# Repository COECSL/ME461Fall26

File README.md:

# ME461Fall26
Lab and HW assignment repository for ME461 Fall 2026

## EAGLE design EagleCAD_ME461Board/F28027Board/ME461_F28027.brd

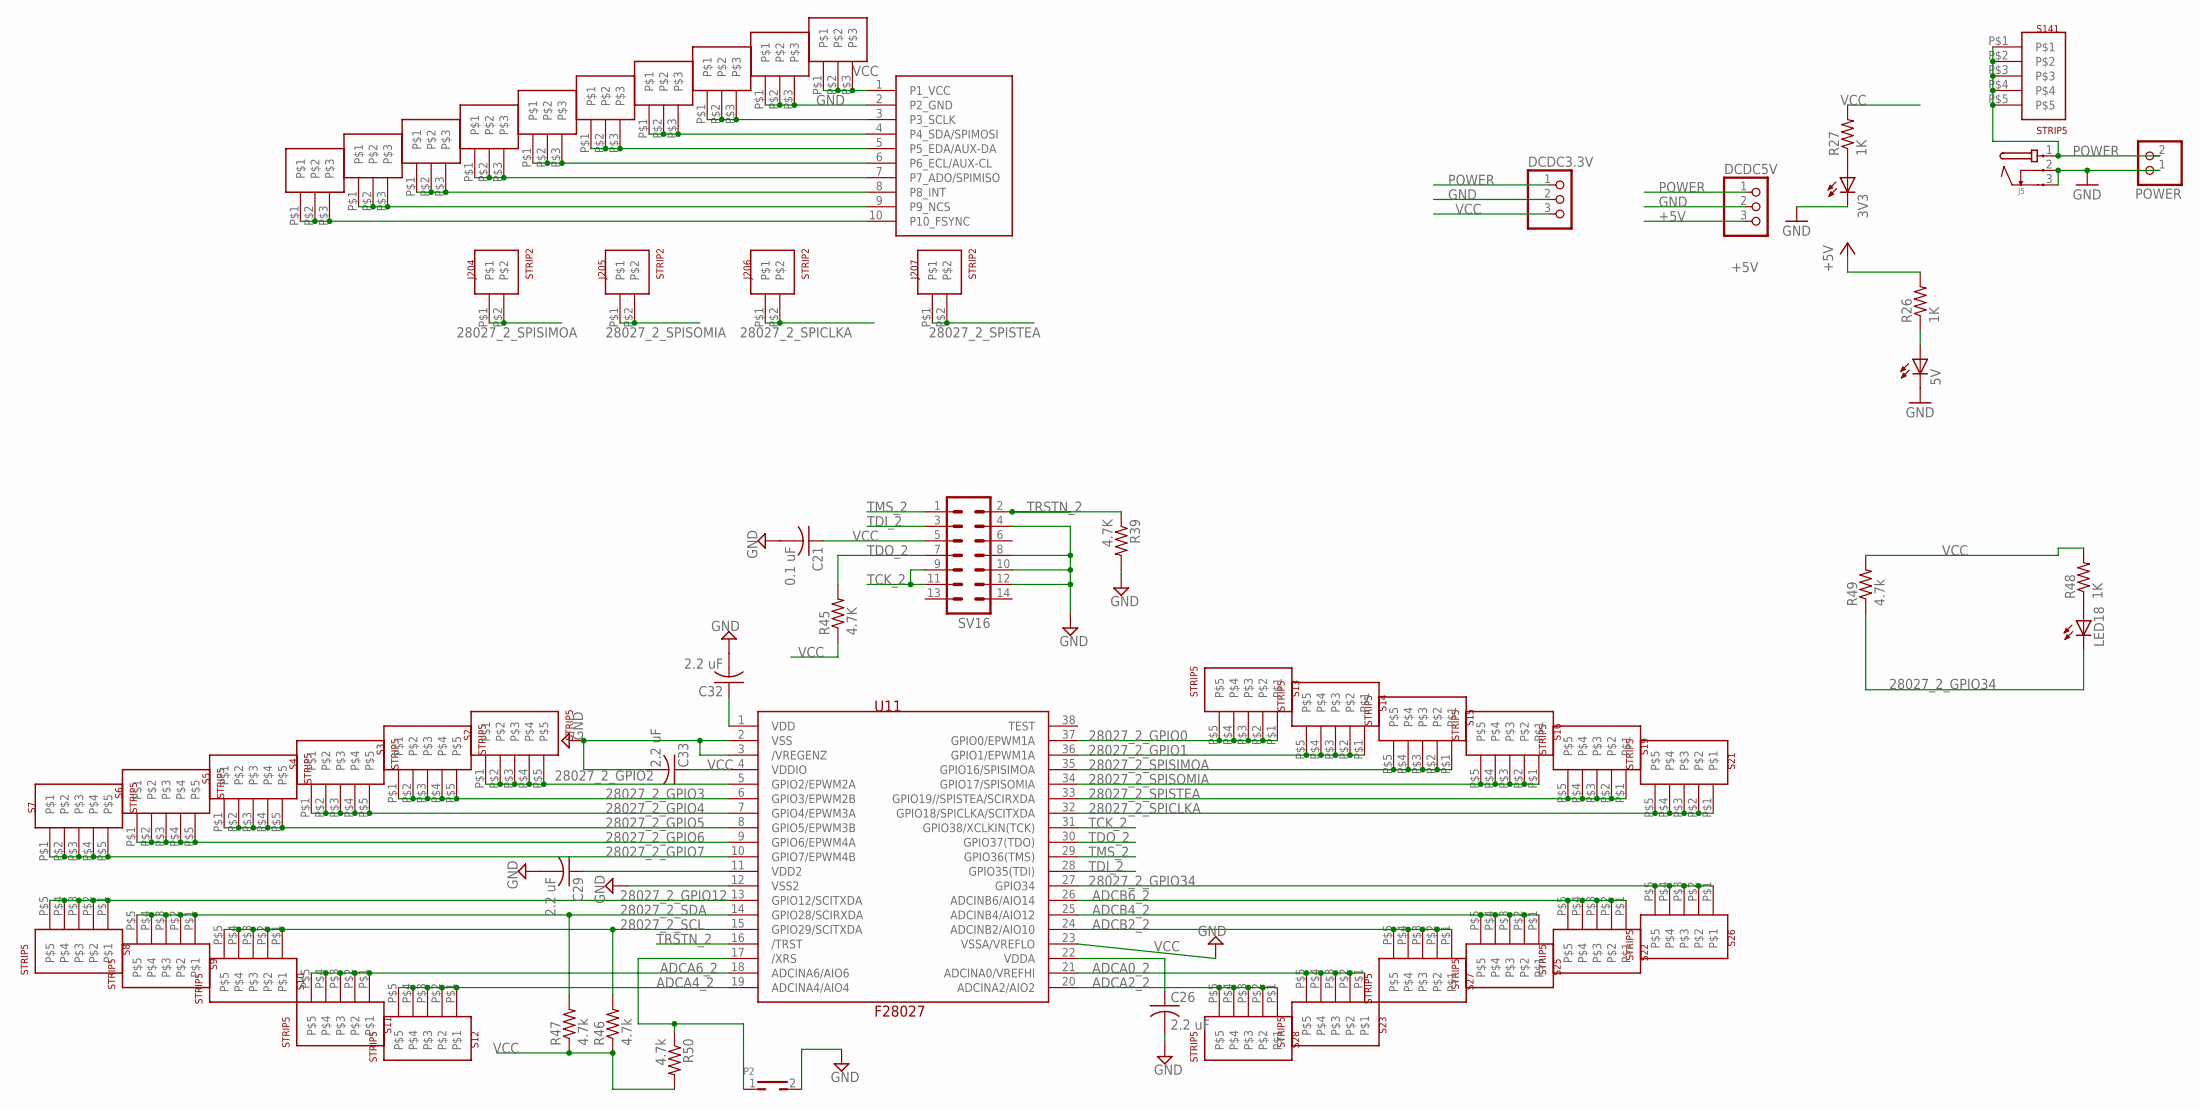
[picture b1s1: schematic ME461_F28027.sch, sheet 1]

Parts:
3V3, 5V: LEDCHIPLED_1206; CHIPLED_1206
C21: 0.1 uF; C1206
C26, C29, C32, C33: 2.2 uF; C1206
DCDC3.3V, DCDC5V: PINHD-1X3; 1X03
J5: JACK-PMS
J123, J124, J125, J126, J127, J128, J129, J130, J131, J132: STRIP3
J204, J205, J206, J207: STRIP2
LED18: LEDCHIPLED_1206; CHIPLED_1206
P2: TH_PUSHBOTTON; TH_PUSHBUTTON
POWER: PINHD-1X2; 1X02
R26, R27, R48: 1K; M1206
R39, R45: 4.7K; M1206
R46, R47, R49, R50: 4.7k; M1206
S2, S3, S4, S5, S6, S7, S8, S9, S10, S11, S12, S13, S14, S15, S16, S19, S21, S22, S23, S25, S26, S27, S28, S141: STRIP5
SV16: MA07-2
U11: F28027; DA38
U$1: MPU-9250-BB

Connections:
28027_2_GPIO0: S13.P$1, S13.P$2, S13.P$3, S13.P$4, S13.P$5, U11.37 (GPIO0/EPWM1A); also elsewhere on the board
28027_2_GPIO1: S14.P$1, S14.P$2, S14.P$3, S14.P$4, S14.P$5, U11.36 (GPIO1/EPWM1A); also elsewhere on the board
28027_2_GPIO2: S2.P$1, S2.P$2, S2.P$3, S2.P$4, S2.P$5, U11.5 (GPIO2/EPWM2A); also elsewhere on the board
28027_2_GPIO3: S3.P$1, S3.P$2, S3.P$3, S3.P$4, S3.P$5, U11.6 (GPIO3/EPWM2B); also elsewhere on the board
28027_2_GPIO4: S4.P$1, S4.P$2, S4.P$3, S4.P$4, S4.P$5, U11.7 (GPIO4/EPWM3A); also elsewhere on the board
28027_2_GPIO5: S5.P$1, S5.P$2, S5.P$3, S5.P$4, S5.P$5, U11.8 (GPIO5/EPWM3B); also elsewhere on the board
28027_2_GPIO6: S6.P$1, S6.P$2, S6.P$3, S6.P$4, S6.P$5, U11.9 (GPIO6/EPWM4A); also elsewhere on the board
28027_2_GPIO7: S7.P$1, S7.P$2, S7.P$3, S7.P$4, S7.P$5, U11.10 (GPIO7/EPWM4B); also elsewhere on the board
28027_2_GPIO12: S8.P$1, S8.P$2, S8.P$3, S8.P$4, S8.P$5, U11.13 (GPIO12/SCITXDA); also elsewhere on the board
28027_2_GPIO34: LED18.C, R49.1, S26.P$1, S26.P$2, S26.P$3, S26.P$4, S26.P$5, U11.27 (GPIO34); also elsewhere on the board
28027_2_SCL: R46.2, S10.P$1, S10.P$2, S10.P$3, S10.P$4, S10.P$5, U11.15 (GPIO29/SCITXDA); also elsewhere on the board
28027_2_SDA: R47.2, S9.P$1, S9.P$2, S9.P$3, S9.P$4, S9.P$5, U11.14 (GPIO28/SCIRXDA); also elsewhere on the board
28027_2_SPICLKA: J206.P$1, J206.P$2, S21.P$1, S21.P$2, S21.P$3, S21.P$4, S21.P$5, U11.32 (GPIO18/SPICLKA/SCITXDA); also elsewhere on the board
28027_2_SPISIMOA: J204.P$1, J204.P$2, S15.P$1, S15.P$2, S15.P$3, S15.P$4, S15.P$5, U11.35 (GPIO16/SPISIMOA); also elsewhere on the board
28027_2_SPISOMIA: J205.P$1, J205.P$2, S16.P$1, S16.P$2, S16.P$3, S16.P$4, S16.P$5, U11.34 (GPIO17/SPISOMIA); also elsewhere on the board
28027_2_SPISTEA: J207.P$1, J207.P$2, S19.P$1, S19.P$2, S19.P$3, S19.P$4, S19.P$5, U11.33 (GPIO19//SPISTEA/SCIRXDA)
+5V: DCDC5V.3, R26.2; also elsewhere on the board
ADCA0_2: S23.P$1, S23.P$2, S23.P$3, S23.P$4, S23.P$5, U11.21 (ADCINA0/VREFHI); also elsewhere on the board
ADCA2_2: S28.P$1, S28.P$2, S28.P$3, S28.P$4, S28.P$5, U11.20 (ADCINA2/AIO2); also elsewhere on the board
ADCA4_2: S12.P$1, S12.P$2, S12.P$3, S12.P$4, S12.P$5, U11.19 (ADCINA4/AIO4); also elsewhere on the board
ADCA6_2: S11.P$1, S11.P$2, S11.P$3, S11.P$4, S11.P$5, U11.18 (ADCINA6/AIO6); also elsewhere on the board
ADCB2_2: S27.P$1, S27.P$2, S27.P$3, S27.P$4, S27.P$5, U11.24 (ADCINB2/AIO10); also elsewhere on the board
ADCB4_2: S25.P$1, S25.P$2, S25.P$3, S25.P$4, S25.P$5, U11.25 (ADCINB4/AIO12); also elsewhere on the board
ADCB6_2: S22.P$1, S22.P$2, S22.P$3, S22.P$4, S22.P$5, U11.26 (ADCINB6/AIO14); also elsewhere on the board
GND: 3V3.C, 5V.C, C21.2, C26.2, C29.2, C32.2, C33.2, DCDC3.3V.2, DCDC5V.2, J5.2, J5.3, J124.P$1, J124.P$2, J124.P$3, P2.2, POWER.1, R39.2, SV16.4, SV16.8, SV16.10, SV16.12, U11.2 (VSS), U11.3 (/VREGENZ), U11.12 (VSS2), U11.23 (VSSA/VREFLO), U$1.2 (P2_GND); also elsewhere on the board
unnamed: 3V3.A, R27.1
unnamed: C32.1, U11.1 (VDD)
unnamed: C29.1, U11.11 (VDD2)
unnamed: P2.1, R50.1, U11.17 (/XRS)
unnamed: LED18.A, R48.1
unnamed: 5V.A, R26.1
unnamed: J125.P$1, J125.P$2, J125.P$3, U$1.3 (P3_SCLK)
unnamed: J126.P$1, J126.P$2, J126.P$3, U$1.4 (P4_SDA/SPIMOSI)
unnamed: J127.P$1, J127.P$2, J127.P$3, U$1.5 (P5_EDA/AUX-DA)
unnamed: J128.P$1, J128.P$2, J128.P$3, U$1.6 (P6_ECL/AUX-CL)
unnamed: J129.P$1, J129.P$2, J129.P$3, U$1.7 (P7_ADO/SPIMISO)
unnamed: J130.P$1, J130.P$2, J130.P$3, U$1.8 (P8_INT)
unnamed: J131.P$1, J131.P$2, J131.P$3, U$1.9 (P9_NCS)
unnamed: J132.P$1, J132.P$2, J132.P$3, U$1.10 (P10_FSYNC)
POWER: DCDC3.3V.1, DCDC5V.1, J5.1, POWER.2, S141.P$1, S141.P$2, S141.P$3, S141.P$4, S141.P$5; also elsewhere on the board
TCK_2: SV16.9, SV16.11, U11.31 (GPIO38/XCLKIN(TCK))
TDI_2: SV16.3, U11.28 (GPIO35(TDI))
TDO_2: R45.2, SV16.7, U11.30 (GPIO37(TDO)); also elsewhere on the board
TMS_2: SV16.1, U11.29 (GPIO36(TMS))
TRSTN_2: R39.1, SV16.2, U11.16 (/TRST)
VCC: C21.1, C26.1, C33.1, DCDC3.3V.3, J123.P$1, J123.P$2, J123.P$3, R27.2, R45.1, R46.1, R47.1, R48.2, R49.2, R50.2, SV16.5, U11.4 (VDDIO), U11.22 (VDDA), U$1.1 (P1_VCC); also elsewhere on the board

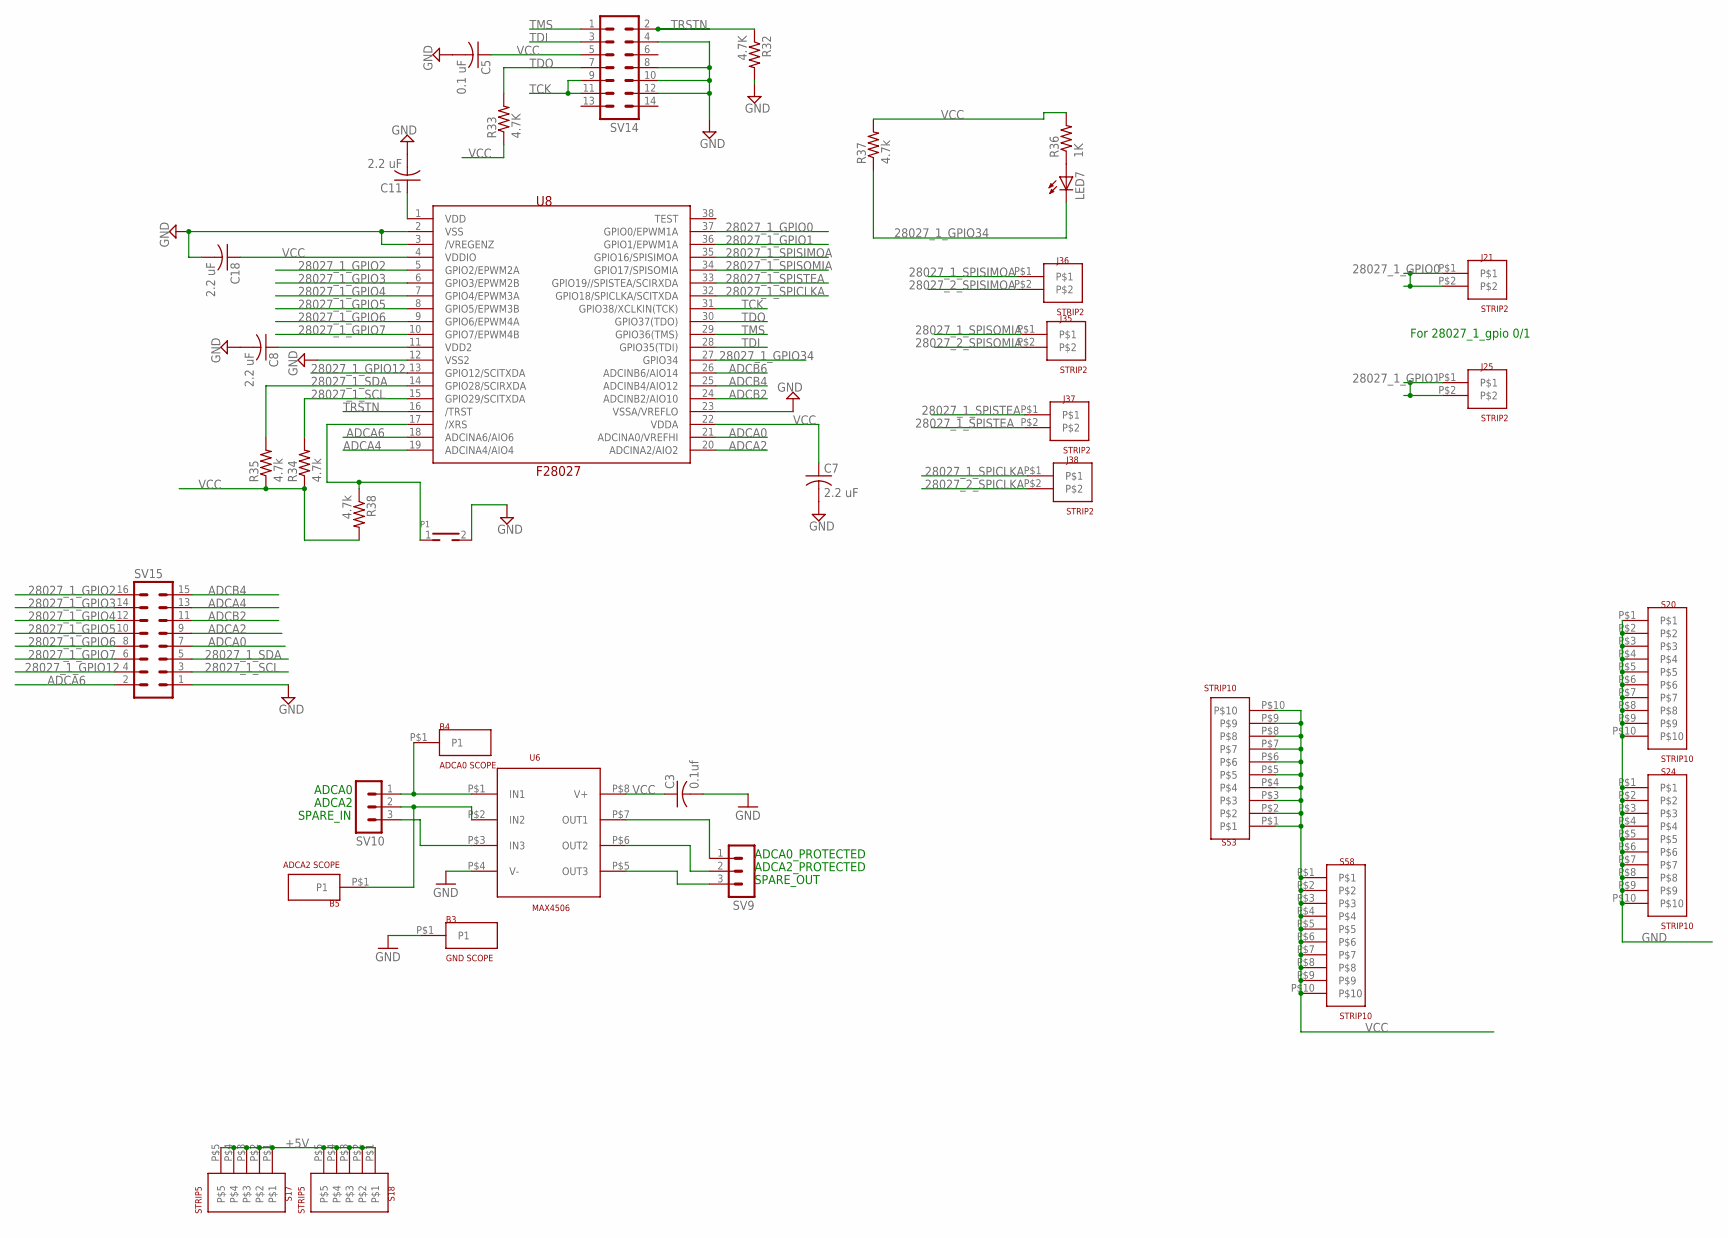
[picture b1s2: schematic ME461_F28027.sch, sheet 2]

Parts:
B3: GND SCOPE; BANANA_MALE
B4: ADCA0 SCOPE; BANANA_MALE
B5: ADCA2 SCOPE; BANANA_MALE
C3: 0.1uf; C1206
C5: 0.1 uF; C1206
C7, C8, C11, C18: 2.2 uF; C1206
J21, J25, J35, J36, J37, J38: STRIP2
LED7: LEDCHIPLED_1206; CHIPLED_1206
P1: TH_PUSHBOTTON; TH_PUSHBUTTON
R32, R33: 4.7K; M1206
R34, R35, R37, R38: 4.7k; M1206
R36: 1K; M1206
S17, S18: STRIP5
S20, S24, S53, S58: STRIP10
SV9, SV10: MA03-1
SV14: MA07-2
SV15: MA08-2
U6: MAX4506; SOIC-8
U8: F28027; DA38

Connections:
28027_1_GPIO0: J21.P$1, J21.P$2, U8.37 (GPIO0/EPWM1A)
28027_1_GPIO1: J25.P$1, J25.P$2, U8.36 (GPIO1/EPWM1A)
28027_1_GPIO2: SV15.16, U8.5 (GPIO2/EPWM2A)
28027_1_GPIO3: SV15.14, U8.6 (GPIO3/EPWM2B)
28027_1_GPIO4: SV15.12, U8.7 (GPIO4/EPWM3A)
28027_1_GPIO5: SV15.10, U8.8 (GPIO5/EPWM3B)
28027_1_GPIO6: SV15.8, U8.9 (GPIO6/EPWM4A)
28027_1_GPIO7: SV15.6, U8.10 (GPIO7/EPWM4B)
28027_1_GPIO12: SV15.4, U8.13 (GPIO12/SCITXDA)
28027_1_GPIO34: LED7.C, R37.1, U8.27 (GPIO34)
28027_1_SCL: R34.2, SV15.3, U8.15 (GPIO29/SCITXDA)
28027_1_SDA: R35.2, SV15.5, U8.14 (GPIO28/SCIRXDA)
28027_1_SPICLKA: J38.P$1, U8.32 (GPIO18/SPICLKA/SCITXDA)
28027_1_SPISIMOA: J36.P$1, U8.35 (GPIO16/SPISIMOA)
28027_1_SPISOMIA: J35.P$1, U8.34 (GPIO17/SPISOMIA)
28027_1_SPISTEA: J37.P$1, J37.P$2, U8.33 (GPIO19//SPISTEA/SCIRXDA)
28027_2_SPICLKA: J38.P$2; also elsewhere on the board
28027_2_SPISIMOA: J36.P$2; also elsewhere on the board
28027_2_SPISOMIA: J35.P$2; also elsewhere on the board
+5V: S17.P$1, S17.P$2, S17.P$3, S17.P$4, S17.P$5, S18.P$1, S18.P$2, S18.P$3, S18.P$4, S18.P$5; also elsewhere on the board
ADCA0: SV15.7, U8.21 (ADCINA0/VREFHI)
ADCA2: SV15.9, U8.20 (ADCINA2/AIO2)
ADCA4: SV15.13, U8.19 (ADCINA4/AIO4)
ADCA6: SV15.2, U8.18 (ADCINA6/AIO6)
ADCB2: SV15.11, U8.24 (ADCINB2/AIO10)
ADCB4: SV15.15, U8.25 (ADCINB4/AIO12)
ADCB6: U8.26 (ADCINB6/AIO14)
GND: B3.P$1, C3.2, C5.2, C7.2, C8.2, C11.2, C18.2, P1.2, R32.2, S20.P$1, S20.P$2, S20.P$3, S20.P$4, S20.P$5, S20.P$6, S20.P$7, S20.P$8, S20.P$9, S20.P$10, S24.P$1, S24.P$2, S24.P$3, S24.P$4, S24.P$5, S24.P$6, S24.P$7, S24.P$8, S24.P$9, S24.P$10, SV14.4, SV14.8, SV14.10, SV14.12, SV15.1, U6.P$4 (V-), U8.2 (VSS), U8.3 (/VREGENZ), U8.12 (VSS2), U8.23 (VSSA/VREFLO); also elsewhere on the board
unnamed: SV9.1, U6.P$7 (OUT1)
unnamed: SV9.2, U6.P$6 (OUT2)
unnamed: SV9.3, U6.P$5 (OUT3)
unnamed: B4.P$1, SV10.1, U6.P$1 (IN1)
unnamed: SV10.3, U6.P$3 (IN3)
unnamed: C11.1, U8.1 (VDD)
unnamed: C8.1, U8.11 (VDD2)
unnamed: P1.1, R38.1, U8.17 (/XRS)
unnamed: LED7.A, R36.1
unnamed: B5.P$1, SV10.2, U6.P$2 (IN2)
TCK: SV14.9, SV14.11, U8.31 (GPIO38/XCLKIN(TCK))
TDI: SV14.3, U8.28 (GPIO35(TDI))
TDO: R33.2, SV14.7, U8.30 (GPIO37(TDO))
TMS: SV14.1, U8.29 (GPIO36(TMS))
TRSTN: R32.1, SV14.2, U8.16 (/TRST)
VCC: C3.1, C5.1, C7.1, C18.1, R33.1, R34.1, R35.1, R36.2, R37.2, R38.2, S53.P$1, S53.P$2, S53.P$3, S53.P$4, S53.P$5, S53.P$6, S53.P$7, S53.P$8, S53.P$9, S53.P$10, S58.P$1, S58.P$2, S58.P$3, S58.P$4, S58.P$5, S58.P$6, S58.P$7, S58.P$8, S58.P$9, S58.P$10, SV14.5, U6.P$8 (V+), U8.4 (VDDIO), U8.22 (VDDA); also elsewhere on the board

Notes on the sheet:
ADCA0
ADCA0_PROTECTED
ADCA2
ADCA2_PROTECTED
SPARE_IN
SPARE_OUT
For 28027_1_gpio 0/1

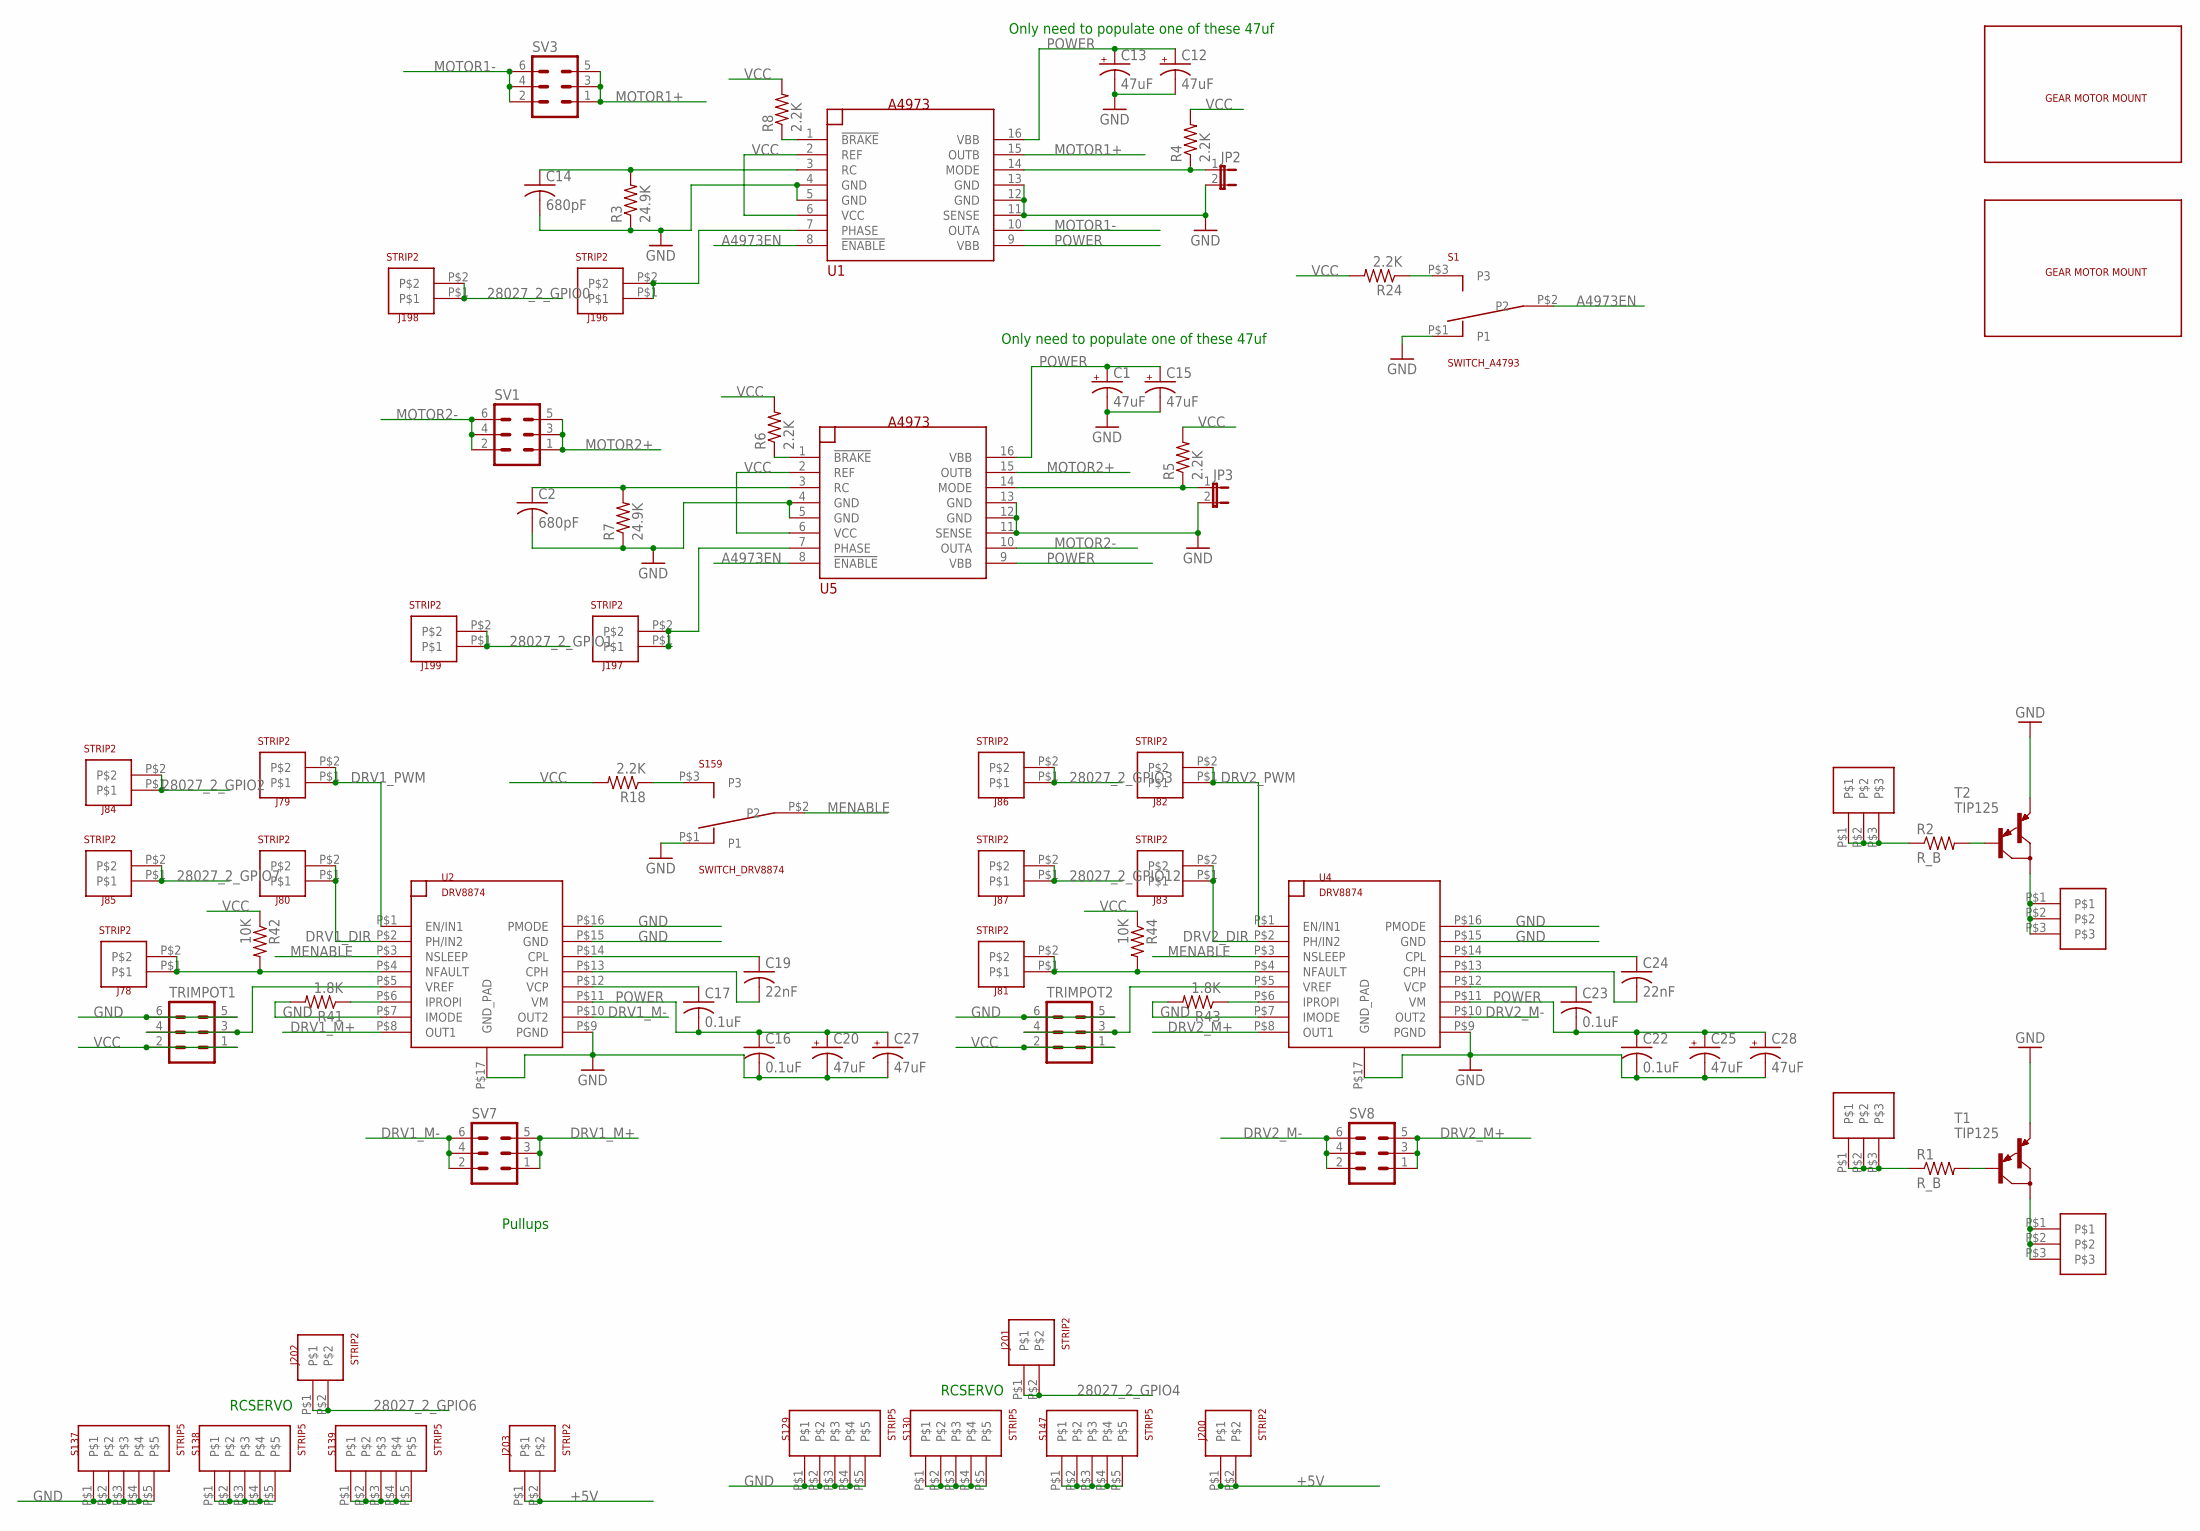
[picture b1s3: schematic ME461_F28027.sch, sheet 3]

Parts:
C1, C12, C13, C15, C20, C25, C27, C28: 47uF; 153CLV-0810
C2, C14: 680pF; C1206
C16, C17, C22, C23: 0.1uF; C1206
C19, C24: 22nF; C1206
J4, J6, J23, J24: STRIP3
J78, J79, J80, J81, J82, J83, J84, J85, J86, J87, J196, J197, J198, J199, J200, J201, J202, J203: STRIP2
JP2, JP3: JP1E; JP1
R1, R2: R_B; 0207/10
R3, R7: 24.9K; M1206
R4, R5, R6, R8, R18, R24: 2.2K; M1206
R41, R43: 1.8K; M1206
R42, R44: 10K; M1206
S1: SWITCH_A4793; SWITCH_SLIDE
S129, S130, S137, S138, S139, S147: STRIP5
S159: SWITCH_DRV8874; SWITCH_SLIDE
SV1, SV3, SV7, SV8: MA03-2
T1, T2: TIP125; TO220
TRIMPOT1, TRIMPOT2: MA03-2
U1, U5: A4973; SO16W
U2, U4: DRV8874; HTSSOP16
U$2, U$3: GEARMOTOR_MOUNT

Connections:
28027_2_GPIO0: J198.P$1, J198.P$2; also elsewhere on the board
28027_2_GPIO1: J199.P$1, J199.P$2; also elsewhere on the board
28027_2_GPIO2: J84.P$1, J84.P$2; also elsewhere on the board
28027_2_GPIO3: J86.P$1, J86.P$2; also elsewhere on the board
28027_2_GPIO4: J201.P$1, J201.P$2; also elsewhere on the board
28027_2_GPIO6: J202.P$1, J202.P$2; also elsewhere on the board
28027_2_GPIO7: J85.P$1, J85.P$2; also elsewhere on the board
28027_2_GPIO12: J87.P$1, J87.P$2; also elsewhere on the board
+5V: J200.P$1, J200.P$2, J203.P$1, J203.P$2; also elsewhere on the board
A4973EN: S1.P$2 (P2), U1.8 (!ENABLE), U5.8 (!ENABLE)
DRV1_DIR: J80.P$1, J80.P$2, U2.P$2 (PH/IN2)
DRV1_M+: SV7.1, SV7.3, SV7.5, U2.P$8 (OUT1)
DRV1_M-: SV7.2, SV7.4, SV7.6, U2.P$10 (OUT2)
DRV1_PWM: J79.P$1, J79.P$2, U2.P$1 (EN/IN1)
DRV2_DIR: J83.P$1, J83.P$2, U4.P$2 (PH/IN2)
DRV2_M+: SV8.1, SV8.3, SV8.5, U4.P$8 (OUT1)
DRV2_M-: SV8.2, SV8.4, SV8.6, U4.P$10 (OUT2)
DRV2_PWM: J82.P$1, J82.P$2, U4.P$1 (EN/IN1)
GND: C1.-, C2.2, C12.-, C13.-, C14.2, C15.-, C16.2, C20.-, C22.2, C25.-, C27.-, C28.-, JP2.2, JP3.2, R3.1, R7.1, R41.2, R43.2, S1.P$1 (P1), S129.P$1, S129.P$2, S129.P$3, S129.P$4, S129.P$5, S137.P$1, S137.P$2, S137.P$3, S137.P$4, S137.P$5, S159.P$1 (P1), T1.3 (E), T2.3 (E), TRIMPOT1.5, TRIMPOT1.6, TRIMPOT2.5, TRIMPOT2.6, U1.4 (GND), U1.5 (GND), U1.11 (SENSE), U1.12 (GND), U1.13 (GND), U2.P$7 (IMODE), U2.P$9 (PGND), U2.P$15 (GND), U2.P$16 (PMODE), U2.P$17 (GND_PAD), U4.P$7 (IMODE), U4.P$9 (PGND), U4.P$15 (GND), U4.P$16 (PMODE), U4.P$17 (GND_PAD), U5.4 (GND), U5.5 (GND), U5.11 (SENSE), U5.12 (GND), U5.13 (GND); also elsewhere on the board
MENABLE: S159.P$2 (P2), U2.P$3 (NSLEEP), U4.P$3 (NSLEEP)
MOTOR1+: SV3.1, SV3.3, SV3.5, U1.15 (OUTB)
MOTOR1-: SV3.2, SV3.4, SV3.6, U1.10 (OUTA)
MOTOR2+: SV1.1, SV1.3, SV1.5, U5.15 (OUTB)
MOTOR2-: SV1.2, SV1.4, SV1.6, U5.10 (OUTA)
unnamed: R24.1, S1.P$3 (P3)
unnamed: S139.P$1, S139.P$2, S139.P$3, S139.P$4, S139.P$5
unnamed: S147.P$1, S147.P$2, S147.P$3, S147.P$4, S147.P$5
unnamed: R2.2, T2.1 (B)
unnamed: R1.2, T1.1 (B)
unnamed: S138.P$1, S138.P$2, S138.P$3, S138.P$4, S138.P$5
unnamed: R6.1, U5.1 (!BRAKE)
unnamed: C2.1, R7.2, U5.3 (RC)
unnamed: R8.1, U1.1 (!BRAKE)
unnamed: C14.1, R3.2, U1.3 (RC)
unnamed: JP2.1, R4.1, U1.14 (MODE)
unnamed: R18.1, S159.P$3 (P3)
unnamed: JP3.1, R5.1, U5.14 (MODE)
unnamed: C19.1, U2.P$14 (CPL)
unnamed: C19.2, U2.P$13 (CPH)
unnamed: C17.1, U2.P$12 (VCP)
unnamed: R43.1, U4.P$6 (IPROPI)
unnamed: R41.1, U2.P$6 (IPROPI)
unnamed: J78.P$1, J78.P$2, R42.2, U2.P$4 (NFAULT)
unnamed: TRIMPOT1.3, TRIMPOT1.4, U2.P$5 (VREF)
unnamed: C24.1, U4.P$14 (CPL)
unnamed: C24.2, U4.P$13 (CPH)
unnamed: C23.1, U4.P$12 (VCP)
unnamed: J81.P$1, J81.P$2, R44.2, U4.P$4 (NFAULT)
unnamed: TRIMPOT2.3, TRIMPOT2.4, U4.P$5 (VREF)
unnamed: S130.P$1, S130.P$2, S130.P$3, S130.P$4, S130.P$5
unnamed: J196.P$1, J196.P$2, U1.7 (PHASE)
unnamed: J197.P$1, J197.P$2, U5.7 (PHASE)
POWER: C1.+, C12.+, C13.+, C15.+, C16.1, C17.2, C20.+, C22.1, C23.2, C25.+, C27.+, C28.+, U1.9 (VBB), U1.16 (VBB), U2.P$11 (VM), U4.P$11 (VM), U5.9 (VBB), U5.16 (VBB); also elsewhere on the board
TR_BASE: J6.P$1, J6.P$2, J6.P$3, R1.1
TR_BASE1: J24.P$1, J24.P$2, J24.P$3, R2.1
TR_LOAD: J4.P$1, J4.P$2, J4.P$3, T1.2 (C)
TR_LOAD1: J23.P$1, J23.P$2, J23.P$3, T2.2 (C)
VCC: R4.2, R5.2, R6.2, R8.2, R18.2, R24.2, R42.1, R44.1, TRIMPOT1.1, TRIMPOT1.2, TRIMPOT2.1, TRIMPOT2.2, U1.2 (REF), U1.6 (VCC), U5.2 (REF), U5.6 (VCC); also elsewhere on the board

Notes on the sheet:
Pullups
RCSERVO
Only need to populate one of these 47uf

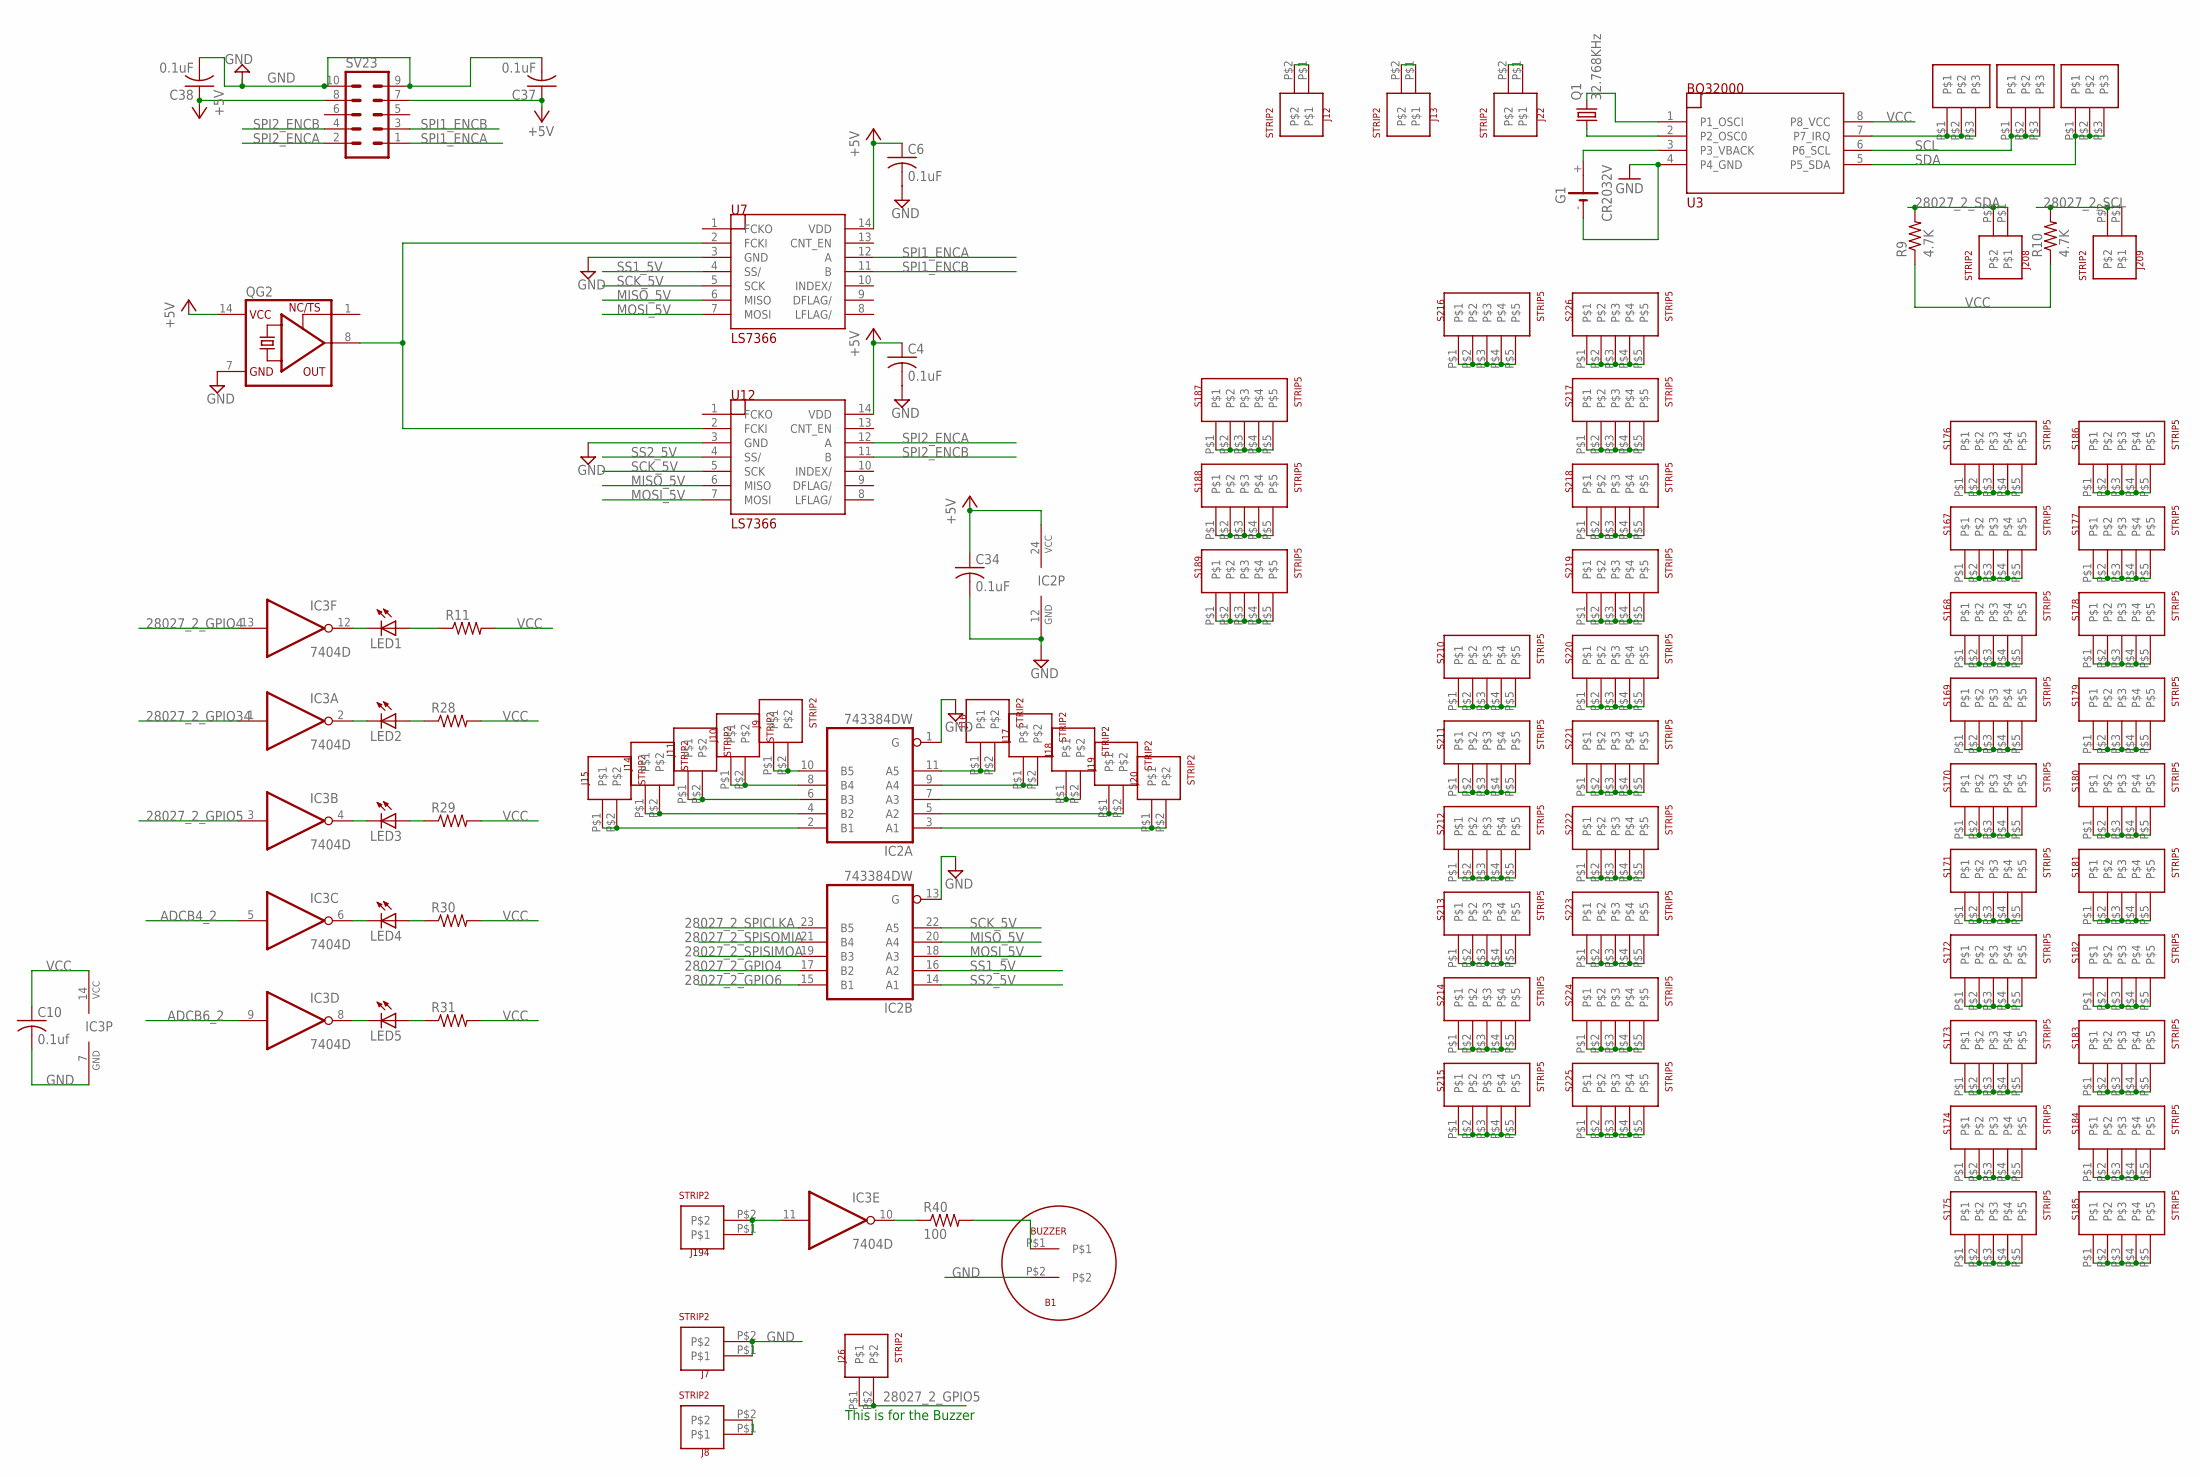
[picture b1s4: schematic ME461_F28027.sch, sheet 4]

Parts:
B1: BUZZER
C4, C6, C34, C37, C38: 0.1uF; C1206
C10: 0.1uf; C1206
G1: CR2032V
IC2: 743384DW; SO24W
IC3: 7404D; SO14
J1, J2, J3: STRIP3
J7, J8, J9, J10, J11, J12, J13, J14, J15, J16, J17, J18, J19, J20, J22, J26, J194, J208, J209: STRIP2
LED1, LED2, LED3, LED4, LED5: LEDCHIPLED_1206; CHIPLED_1206
Q1: 32.768KHz; TC26H
QG2: XO-14; DIL14S
R9, R10: 4.7K; R1206
R11, R28, R29, R30, R31: R-US_R1206; R1206
R40: 100; R1206
S167, S168, S169, S170, S171, S172, S173, S174, S175, S176, S177, S178, S179, S180, S181, S182, S183, S184, S185, S186, S187, S188, S189, S210, S211, S212, S213, S214, S215, S216, S217, S218, S219, S220, S221, S222, S223, S224, S225, S226: STRIP5
SV23: MA05-2
U3: BQ32000; SO08
U7, U12: LS7366; SO14

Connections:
28027_2_GPIO4: IC2.17 (B2), IC3.13 (I); also elsewhere on the board
28027_2_GPIO5: IC3.3 (I), J26.P$1, J26.P$2; also elsewhere on the board
28027_2_GPIO6: IC2.15 (B1); also elsewhere on the board
28027_2_GPIO34: IC3.1 (I); also elsewhere on the board
28027_2_SCL: J209.P$1, J209.P$2, R10.2; also elsewhere on the board
28027_2_SDA: J208.P$1, J208.P$2, R9.2; also elsewhere on the board
28027_2_SPICLKA: IC2.23 (B5); also elsewhere on the board
28027_2_SPISIMOA: IC2.19 (B3); also elsewhere on the board
28027_2_SPISOMIA: IC2.21 (B4); also elsewhere on the board
+5V: C4.1, C6.1, C34.1, C37.1, C38.1, IC2.24 (VCC), QG2.14 (VCC), SV23.7, SV23.8, U7.14 (VDD), U12.14 (VDD); also elsewhere on the board
A1: IC2.3 (A1), J20.P$1, J20.P$2
A2: IC2.5 (A2), J19.P$1, J19.P$2
A3: IC2.7 (A3), J18.P$1, J18.P$2
A4: IC2.9 (A4), J17.P$1, J17.P$2
A5: IC2.11 (A5), J16.P$1, J16.P$2
ADCB4_2: IC3.5 (I); also elsewhere on the board
ADCB6_2: IC3.9 (I); also elsewhere on the board
B1: IC2.2 (B1), J15.P$1, J15.P$2
B2: IC2.4 (B2), J14.P$1, J14.P$2
B3: IC2.6 (B3), J11.P$1, J11.P$2
B4: IC2.8 (B4), J10.P$1, J10.P$2
B5: IC2.10 (B5), J9.P$1, J9.P$2
GND: B1.P$2, C4.2, C6.2, C10.2, C34.2, C37.2, C38.2, G1.-, IC2.1 (G), IC2.12 (GND), IC2.13 (G), IC3.7 (GND), J7.P$1, J7.P$2, QG2.7 (GND), SV23.9, SV23.10, U3.4 (P4_GND), U7.3 (GND), U12.3 (GND); also elsewhere on the board
MISO_5V: IC2.20 (A4), U7.6 (MISO), U12.6 (MISO)
MOSI_5V: IC2.18 (A3), U7.7 (MOSI), U12.7 (MOSI)
unnamed: J12.P$1, J12.P$2
unnamed: J13.P$1, J13.P$2
unnamed: J22.P$1, J22.P$2
unnamed: QG2.8 (OUT), U7.2 (FCKI), U12.2 (FCKI)
unnamed: IC3.12 (O), LED1.C
unnamed: LED1.A, R11.1
unnamed: J8.P$1, J8.P$2
unnamed: IC3.10 (O), R40.1
unnamed: B1.P$1, R40.2
unnamed: Q1.1, U3.2 (P2_OSC0)
unnamed: Q1.2, U3.1 (P1_OSCI)
unnamed: J1.P$1, J1.P$2, J1.P$3, U3.7 (P7_IRQ)
unnamed: G1.+, U3.3 (P3_VBACK)
unnamed: S167.P$1, S167.P$2, S167.P$3, S167.P$4, S167.P$5
unnamed: S168.P$1, S168.P$2, S168.P$3, S168.P$4, S168.P$5
unnamed: S169.P$1, S169.P$2, S169.P$3, S169.P$4, S169.P$5
unnamed: S170.P$1, S170.P$2, S170.P$3, S170.P$4, S170.P$5
unnamed: S171.P$1, S171.P$2, S171.P$3, S171.P$4, S171.P$5
unnamed: S172.P$1, S172.P$2, S172.P$3, S172.P$4, S172.P$5
unnamed: S173.P$1, S173.P$2, S173.P$3, S173.P$4, S173.P$5
unnamed: S174.P$1, S174.P$2, S174.P$3, S174.P$4, S174.P$5
unnamed: S175.P$1, S175.P$2, S175.P$3, S175.P$4, S175.P$5
unnamed: S176.P$1, S176.P$2, S176.P$3, S176.P$4, S176.P$5
unnamed: S177.P$1, S177.P$2, S177.P$3, S177.P$4, S177.P$5
unnamed: S178.P$1, S178.P$2, S178.P$3, S178.P$4, S178.P$5
unnamed: S179.P$1, S179.P$2, S179.P$3, S179.P$4, S179.P$5
unnamed: S180.P$1, S180.P$2, S180.P$3, S180.P$4, S180.P$5
unnamed: S181.P$1, S181.P$2, S181.P$3, S181.P$4, S181.P$5
unnamed: S182.P$1, S182.P$2, S182.P$3, S182.P$4, S182.P$5
unnamed: S183.P$1, S183.P$2, S183.P$3, S183.P$4, S183.P$5
unnamed: S184.P$1, S184.P$2, S184.P$3, S184.P$4, S184.P$5
unnamed: S185.P$1, S185.P$2, S185.P$3, S185.P$4, S185.P$5
unnamed: S186.P$1, S186.P$2, S186.P$3, S186.P$4, S186.P$5
unnamed: S187.P$1, S187.P$2, S187.P$3, S187.P$4, S187.P$5
unnamed: S188.P$1, S188.P$2, S188.P$3, S188.P$4, S188.P$5
unnamed: S189.P$1, S189.P$2, S189.P$3, S189.P$4, S189.P$5
unnamed: S210.P$1, S210.P$2, S210.P$3, S210.P$4, S210.P$5
unnamed: S211.P$1, S211.P$2, S211.P$3, S211.P$4, S211.P$5
unnamed: S212.P$1, S212.P$2, S212.P$3, S212.P$4, S212.P$5
unnamed: S213.P$1, S213.P$2, S213.P$3, S213.P$4, S213.P$5
unnamed: S214.P$1, S214.P$2, S214.P$3, S214.P$4, S214.P$5
unnamed: S215.P$1, S215.P$2, S215.P$3, S215.P$4, S215.P$5
unnamed: S216.P$1, S216.P$2, S216.P$3, S216.P$4, S216.P$5
unnamed: S217.P$1, S217.P$2, S217.P$3, S217.P$4, S217.P$5
unnamed: S218.P$1, S218.P$2, S218.P$3, S218.P$4, S218.P$5
unnamed: S219.P$1, S219.P$2, S219.P$3, S219.P$4, S219.P$5
unnamed: S220.P$1, S220.P$2, S220.P$3, S220.P$4, S220.P$5
unnamed: S221.P$1, S221.P$2, S221.P$3, S221.P$4, S221.P$5
unnamed: S222.P$1, S222.P$2, S222.P$3, S222.P$4, S222.P$5
unnamed: S223.P$1, S223.P$2, S223.P$3, S223.P$4, S223.P$5
unnamed: S224.P$1, S224.P$2, S224.P$3, S224.P$4, S224.P$5
unnamed: S225.P$1, S225.P$2, S225.P$3, S225.P$4, S225.P$5
unnamed: S226.P$1, S226.P$2, S226.P$3, S226.P$4, S226.P$5
unnamed: IC3.2 (O), LED2.C
unnamed: LED2.A, R28.1
unnamed: IC3.4 (O), LED3.C
unnamed: LED3.A, R29.1
unnamed: IC3.6 (O), LED4.C
unnamed: LED4.A, R30.1
unnamed: IC3.8 (O), LED5.C
unnamed: LED5.A, R31.1
unnamed: IC3.11 (I), J194.P$1, J194.P$2
SCK_5V: IC2.22 (A5), U7.5 (SCK), U12.5 (SCK)
SCL: J2.P$1, J2.P$2, J2.P$3, U3.6 (P6_SCL)
SDA: J3.P$1, J3.P$2, J3.P$3, U3.5 (P5_SDA)
SPI1_ENCA: SV23.1, U7.12 (A)
SPI1_ENCB: SV23.3, U7.11 (B)
SPI2_ENCA: SV23.2, U12.12 (A)
SPI2_ENCB: SV23.4, U12.11 (B)
SS1_5V: IC2.16 (A2), U7.4 (SS/)
SS2_5V: IC2.14 (A1), U12.4 (SS/)
VCC: C10.1, IC3.14 (VCC), R9.1, R10.1, R11.2, R28.2, R29.2, R30.2, R31.2, U3.8 (P8_VCC); also elsewhere on the board

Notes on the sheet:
This is for the Buzzer
